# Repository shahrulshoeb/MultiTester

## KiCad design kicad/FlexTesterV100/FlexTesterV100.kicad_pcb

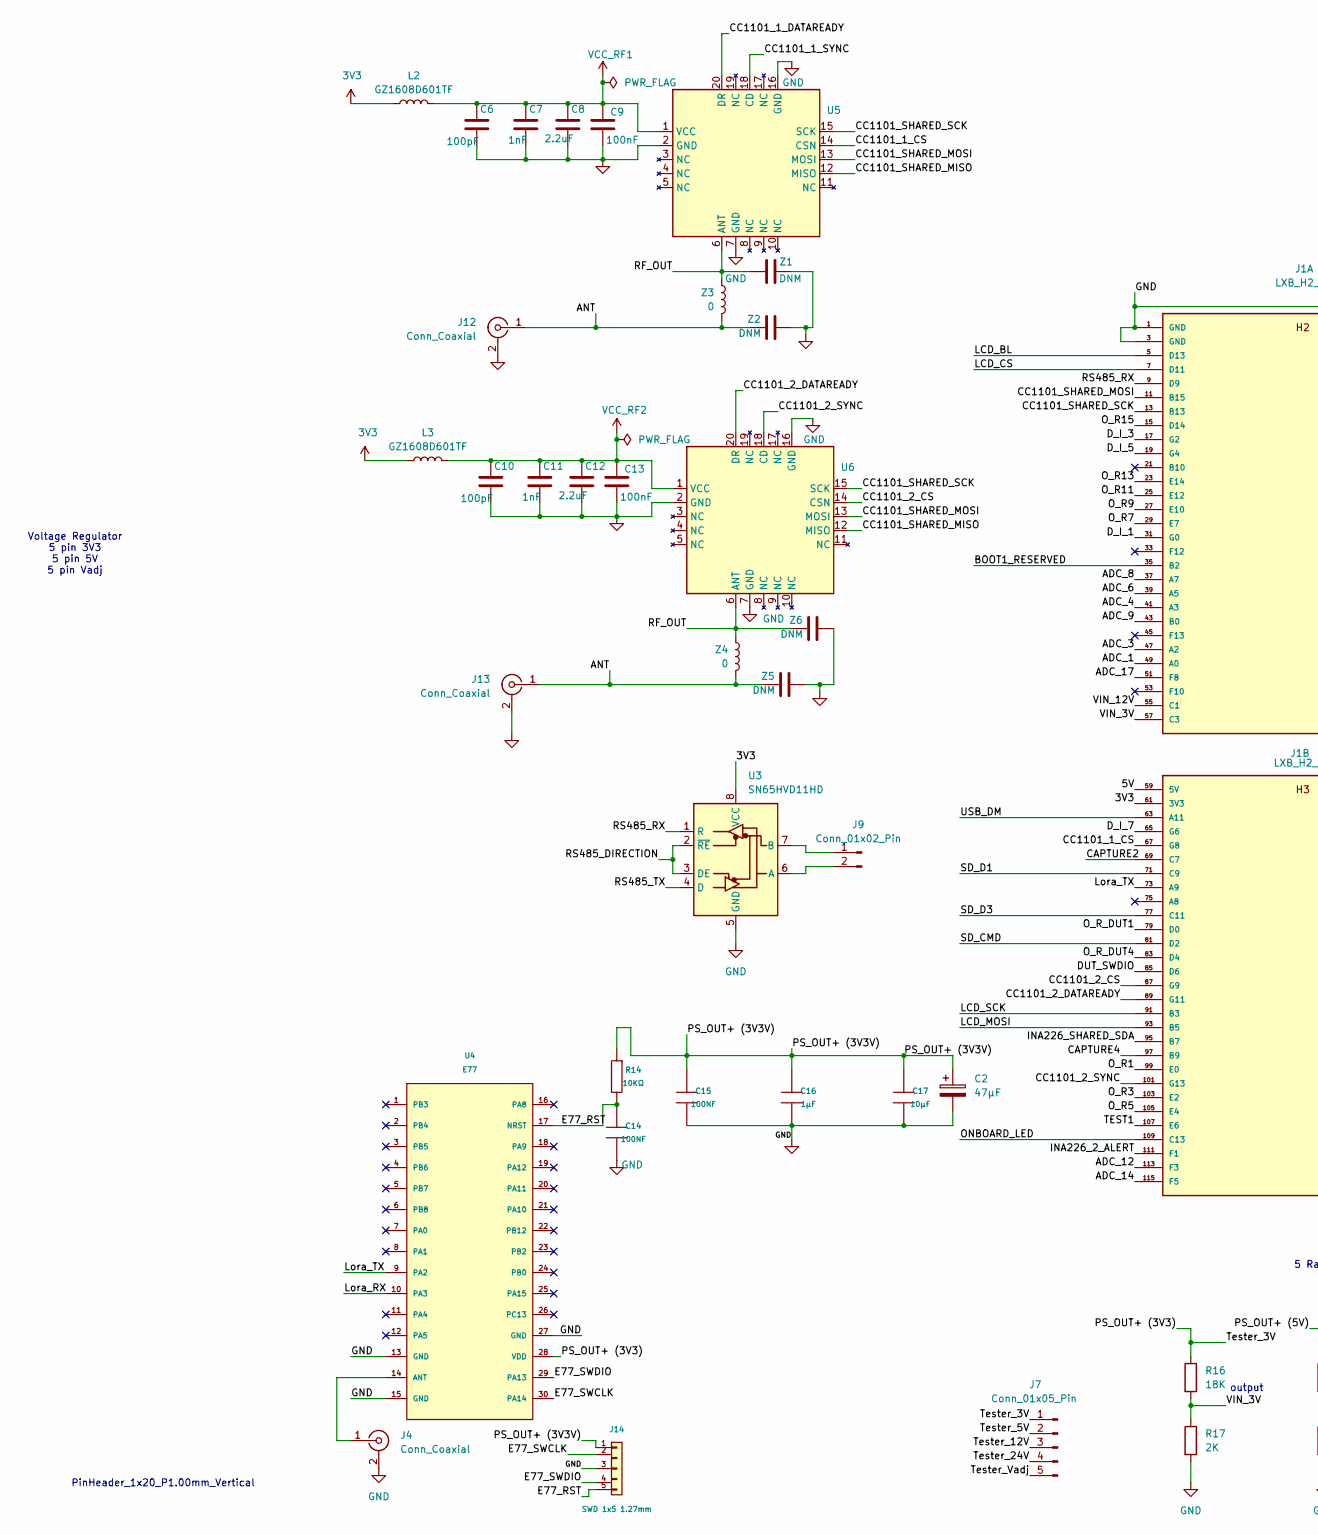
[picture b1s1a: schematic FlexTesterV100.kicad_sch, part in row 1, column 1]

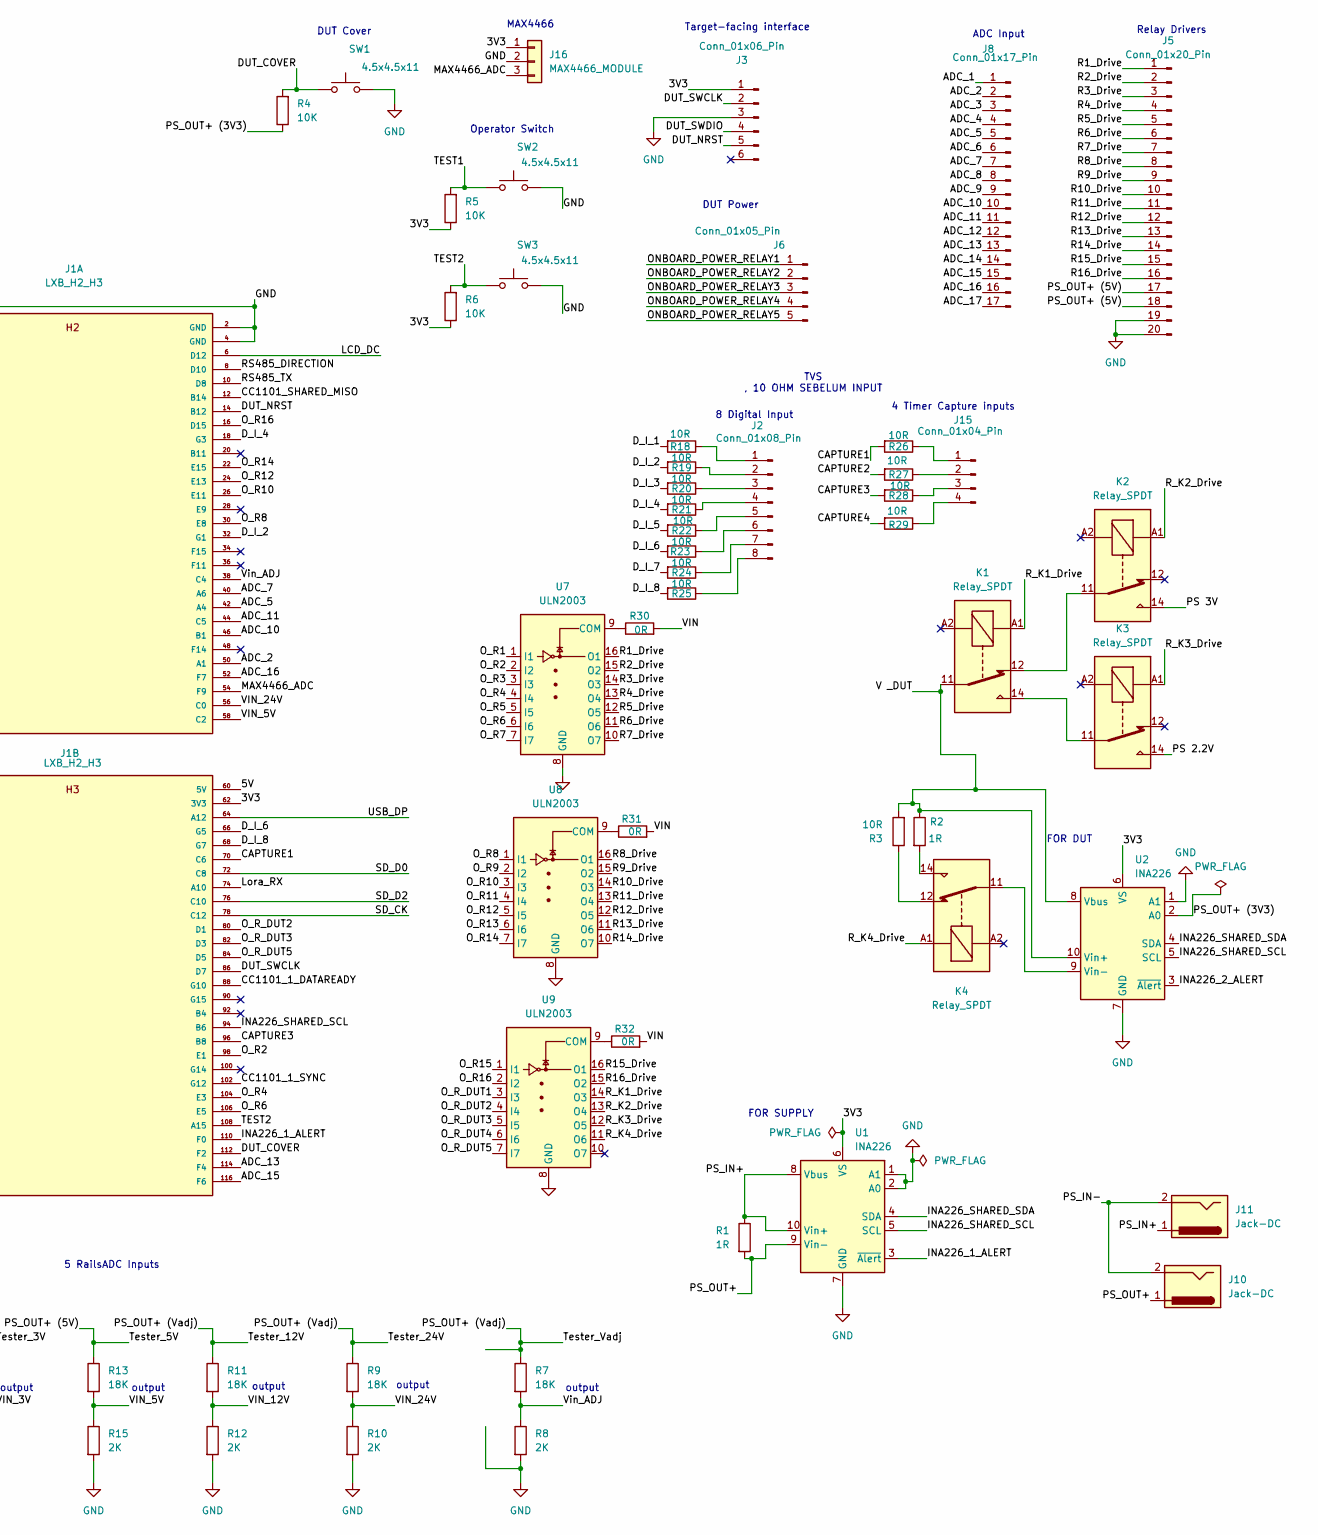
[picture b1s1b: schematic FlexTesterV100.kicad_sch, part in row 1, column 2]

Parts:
C2: 47μF; CP_EIA-7343-31_Kemet-D_HandSolder
C6, C10: 100pF; C_0603_1608Metric_Pad1.08x0.95mm_HandSolder
C7, C11: 1nF; C_0603_1608Metric_Pad1.08x0.95mm_HandSolder
C8, C12: 2.2uF; C_0603_1608Metric_Pad1.08x0.95mm_HandSolder
C9, C13: 100nF; C_0603_1608Metric_Pad1.08x0.95mm_HandSolder
C14, C15: 100NF; C0603
C16: 1μF; C0603
C17: 10μF; C0603
J1: LXB_H2_H3
J2: Conn_01x08_Pin; PinHeader_1x08_P1.00mm_Vertical
J3: Conn_01x06_Pin; PinHeader_1x06_P1.00mm_Vertical
J4, J12, J13: Conn_Coaxial; SMA_Amphenol_132203-12_Horizontal
J5: Conn_01x20_Pin; PinHeader_1x20_P1.00mm_Vertical
J6, J7: Conn_01x05_Pin; PinHeader_1x05_P1.00mm_Vertical
J8: Conn_01x17_Pin; PinHeader_1x17_P1.00mm_Vertical
J9: Conn_01x02_Pin; Terminal_2Pin_P3.50mm
J10, J11: Jack-DC
J14: SWD 1x5 1.27mm; PinHeader_1x05_P1.27mm_Vertical
J15: Conn_01x04_Pin; PinHeader_1x04_P1.00mm_Vertical
J16: MAX4466_MODULE; PinHeader_1x03_P1.00mm_Vertical
K1, K2, K3, K4: Relay_SPDT; Relay_SPDT_Hongfa_JQC-3FF_0XX-1Z
L2, L3: GZ1608D601TF; L_0603_1608Metric_Pad1.05x0.95mm_HandSolder
R1, R2: 1R; R0603
R3, R18, R19, R20, R21, R22, R23, R24, R25, R26, R27, R28, R29: 10R; R0603
R4, R5, R6: 10K; R0603
R7, R9, R11, R13, R16: 18K; R0603
R8, R10, R12, R15, R17: 2K; R0603
R14: 10KΩ; R0603
R30: 0R; R_0603_1608Metric_Pad0.98x0.95mm_HandSolder
R31, R32: 0R; R0603
SW1, SW2, SW3: 4.5x4.5x11; SW_SPST_45x45x110
U1, U2: INA226; TSSOP-10_3x3mm_P0.5mm
U3: SN65HVD11HD; SOIC-8_3.9x4.9mm_P1.27mm
U4: E77; E77-900M22S_Mark1
U5, U6: E07_400MM10_Pitch1.27mm
U7, U8, U9: ULN2003; JEITA_SOIC-16_3.9x9.9mm_P1.27mm
Z1, Z2, Z5, Z6: DNM; C_0603_1608Metric_Pad1.08x0.95mm_HandSolder
Z3, Z4: 0; L_0603_1608Metric_Pad1.05x0.95mm_HandSolder

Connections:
3V3: J1.61 (3V3), J1.62 (3V3), J3.1, J16.1, L2.1, L3.1, R5.1, R6.1, U1.6 (VS), U2.6 (VS), U3.8 (VCC)
/5V: J1.59 (5V), J1.60 (5V)
/ADC_1: J1.49 (A0), J8.1
/ADC_2: J1.50 (A1), J8.2
/ADC_3: J1.47 (A2), J8.3
/ADC_4: J1.41 (A3), J8.4
/ADC_5: J1.42 (A4), J8.5
/ADC_6: J1.39 (A5), J8.6
/ADC_7: J1.40 (A6), J8.7
/ADC_8: J1.37 (A7), J8.8
/ADC_9: J1.43 (B0), J8.9
/ADC_10: J1.46 (B1), J8.10
/ADC_11: J1.44 (C5), J8.11
/ADC_12: J1.113 (F3), J8.12
/ADC_13: J1.114 (F4), J8.13
/ADC_14: J1.115 (F5), J8.14
/ADC_15: J1.116 (F6), J8.15
/ADC_16: J1.52 (F7), J8.16
/ADC_17: J1.51 (F8), J8.17
/ANT: J12.1 (In), J13.1 (In), Z2.1, Z3.1, Z4.1, Z5.1
/BOOT1_RESERVED: J1.35 (B2)
/CAPTURE1: J1.70 (C6), R26.2
/CAPTURE2: J1.69 (C7), R27.2
/CAPTURE3: J1.96 (B8), R28.2
/CAPTURE4: J1.97 (B9), R29.2
/CC1101_1_CS: J1.67 (G8), U5.14 (CSN)
/CC1101_1_DATAREADY: J1.88 (G10), U5.20 (DR)
/CC1101_1_SYNC: J1.102 (G12), U5.18 (CD)
/CC1101_2_CS: J1.87 (G9), U6.14 (CSN)
/CC1101_2_DATAREADY: J1.89 (G11), U6.20 (DR)
/CC1101_2_SYNC: J1.101 (G13), U6.18 (CD)
/CC1101_SHARED_MISO: J1.12 (B14), U5.12 (MISO), U6.12 (MISO)
/CC1101_SHARED_MOSI: J1.11 (B15), U5.13 (MOSI), U6.13 (MOSI)
/CC1101_SHARED_SCK: J1.13 (B13), U5.15 (SCK), U6.15 (SCK)
/DUT_COVER: J1.112 (F2), R4.2, SW1.1
/DUT_NRST: J1.14 (B12), J3.5
/DUT_SWCLK: J1.86 (D7), J3.2
/DUT_SWDIO: J1.85 (D6), J3.4
/D_I_1: J1.31 (G0), R18.2
/D_I_2: J1.32 (G1), R19.2
/D_I_3: J1.17 (G2), R20.2
/D_I_4: J1.18 (G3), R21.2
/D_I_5: J1.19 (G4), R22.2
/D_I_6: J1.66 (G5), R23.2
/D_I_7: J1.65 (G6), R24.2
/D_I_8: J1.68 (G7), R25.2
/E77_RST: C14.1, J14.5, R14.2, U4.17 (NRST)
/E77_SWCLK: J14.2, U4.30 (PA14)
/E77_SWDIO: J14.4, U4.29 (PA13)
/INA226_1_ALERT: J1.110 (F0), U1.3 (~Alert)
/INA226_2_ALERT: J1.111 (F1), U2.3 (~Alert)
/INA226_SHARED_SCL: J1.94 (B6), U1.5 (SCL), U2.5 (SCL)
/INA226_SHARED_SDA: J1.95 (B7), U1.4 (SDA), U2.4 (SDA)
/LCD_BL: J1.5 (D13)
/LCD_CS: J1.7 (D11)
/LCD_DC: J1.6 (D12)
/LCD_MOSI: J1.93 (B5)
/LCD_SCK: J1.91 (B3)
/Lora_RX: J1.74 (A10), U4.10 (PA3)
/Lora_TX: J1.73 (A9), U4.9 (PA2)
/MAX4466_ADC: J1.54 (F9), J16.3
/ONBOARD_LED: J1.109 (C13)
/ONBOARD_POWER_RELAY1: J6.1
/ONBOARD_POWER_RELAY2: J6.2
/ONBOARD_POWER_RELAY3: J6.3
/ONBOARD_POWER_RELAY4: J6.4
/ONBOARD_POWER_RELAY5: J6.5
/O_R1: J1.99 (E0), U7.1 (I1)
/O_R2: J1.98 (E1), U7.2 (I2)
/O_R3: J1.103 (E2), U7.3 (I3)
/O_R4: J1.104 (E3), U7.4 (I4)
/O_R5: J1.105 (E4), U7.5 (I5)
/O_R6: J1.106 (E5), U7.6 (I6)
/O_R7: J1.29 (E7), U7.7 (I7)
/O_R8: J1.30 (E8), U8.1 (I1)
/O_R9: J1.27 (E10), U8.2 (I2)
/O_R10: J1.26 (E11), U8.3 (I3)
/O_R11: J1.25 (E12), U8.4 (I4)
/O_R12: J1.24 (E13), U8.5 (I5)
/O_R13: J1.23 (E14), U8.6 (I6)
/O_R14: J1.22 (E15), U8.7 (I7)
/O_R15: J1.15 (D14), U9.1 (I1)
/O_R16: J1.16 (D15), U9.2 (I2)
/O_R_DUT1: J1.79 (D0), U9.3 (I3)
/O_R_DUT2: J1.80 (D1), U9.4 (I4)
/O_R_DUT3: J1.82 (D3), U9.5 (I5)
/O_R_DUT4: J1.83 (D4), U9.6 (I6)
/O_R_DUT5: J1.84 (D5), U9.7 (I7)
/PS 2.2V: K3.14
/PS 3V: K2.14
/PS_IN+: J11.1, R1.1, U1.8 (Vbus), U1.10 (Vin+)
/PS_OUT+: J10.1, R1.2, U1.9 (Vin-)
/PS_OUT+ (3V3): J7.1, R4.1, R16.1, U2.2 (A0), U4.28 (VDD)
/PS_OUT+ (3V3V): C2.1, C15.1, C16.1, C17.1, J14.1, R14.1
/PS_OUT+ (5V): J5.17, J5.18, J7.2, R13.1
/PS_OUT+ (Vadj): J7.3, J7.4, J7.5, R7.1, R9.1, R11.1
/R1_Drive: J5.1, U7.16 (O1)
/R2_Drive: J5.2, U7.15 (O2)
/R3_Drive: J5.3, U7.14 (O3)
/R4_Drive: J5.4, U7.13 (O4)
/R5_Drive: J5.5, U7.12 (O5)
/R6_Drive: J5.6, U7.11 (O6)
/R7_Drive: J5.7, U7.10 (O7)
/R8_Drive: J5.8, U8.16 (O1)
/R9_Drive: J5.9, U8.15 (O2)
/R10_Drive: J5.10, U8.14 (O3)
/R11_Drive: J5.11, U8.13 (O4)
/R12_Drive: J5.12, U8.12 (O5)
/R13_Drive: J5.13, U8.11 (O6)
/R14_Drive: J5.14, U8.10 (O7)
/R15_Drive: J5.15, U9.16 (O1)
/R16_Drive: J5.16, U9.15 (O2)
/RF_OUT: U5.6 (ANT), U6.6 (ANT), Z1.2, Z3.2, Z4.2, Z6.1
/RS485_DIRECTION: J1.8 (D10), U3.2 (~RE), U3.3 (DE)
/RS485_RX: J1.9 (D9), U3.1 (R)
/RS485_TX: J1.10 (D8), U3.4 (D)
/R_K1_Drive: K1.A1, U9.14 (O3)
/R_K2_Drive: K2.A1, U9.13 (O4)
/R_K3_Drive: K3.A1, U9.12 (O5)
/R_K4_Drive: K4.A1, U9.11 (O6)
/SD_CK: J1.78 (C12)
/SD_CMD: J1.81 (D2)
/SD_D0: J1.72 (C8)
/SD_D1: J1.71 (C9)
/SD_D2: J1.76 (C10)
/SD_D3: J1.77 (C11)
/TEST1: J1.107 (E6), R5.2, SW2.1
/TEST2: J1.108 (A15), R6.2, SW3.1
/USB_DM: J1.63 (A11)
/USB_DP: J1.64 (A12)
/V _DUT: K1.11, R2.1, R3.2, U2.8 (Vbus), U2.10 (Vin+)
/VIN: R30.2, R31.2, R32.2
/VIN_3V: J1.57 (C3), R16.2, R17.1
/VIN_5V: J1.58 (C2), R13.2, R15.1
/VIN_12V: J1.55 (C1), R11.2, R12.1
/VIN_24V: J1.56 (C0), R9.2, R10.1
/Vin_ADJ: J1.38 (C4), R7.2, R8.1
GND: C2.2, C6.2, C7.2, C8.2, C9.2, C10.2, C11.2, C12.2, C13.2, C14.2, C15.2, C16.2, C17.2, J1.1 (GND), J1.2 (GND), J1.3 (GND), J1.4 (GND), J3.3, J4.2 (Ext), J5.19, J5.20, J12.2 (Ext), J13.2 (Ext), J14.3, J16.2, R8.2, R10.2, R12.2, R15.2, R17.2, SW1.2, SW2.2, SW3.2, U1.1 (A1), U1.2 (A0), U1.7 (GND), U2.1 (A1), U2.7 (GND), U3.5 (GND), U4.13 (GND), U4.15 (GND), U4.27 (GND), U5.2 (GND), U5.7 (GND), U5.16 (GND), U6.2 (GND), U6.7 (GND), U6.16 (GND), U7.8 (GND), U8.8 (GND), U9.8 (GND), Z1.1, Z2.2, Z5.2, Z6.2
unnamed: J2.1, R18.1
unnamed: J2.2, R19.1
unnamed: J2.3, R20.1
unnamed: J2.4, R21.1
unnamed: J2.5, R22.1
unnamed: J2.6, R23.1
unnamed: J2.7, R24.1
unnamed: J2.8, R25.1
unnamed: J4.1 (In), U4.14 (ANT)
unnamed: J9.1, U3.7 (B)
unnamed: J9.2, U3.6 (A)
unnamed: J10.2, J11.2
unnamed: J15.1, R26.1
unnamed: J15.2, R27.1
unnamed: J15.3, R28.1
unnamed: J15.4, R29.1
unnamed: K1.12, K2.11
unnamed: K1.14, K3.11
unnamed: K4.12, R3.1
unnamed: K4.14, R2.2
unnamed: K4.11, U2.9 (Vin-)
unnamed: R30.1, U7.9 (COM)
unnamed: R31.1, U8.9 (COM)
unnamed: R32.1, U9.9 (COM)
VCC_RF1: C6.1, C7.1, C8.1, C9.1, L2.2, U5.1 (VCC)
VCC_RF2: C10.1, C11.1, C12.1, C13.1, L3.2, U6.1 (VCC)

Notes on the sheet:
Voltage Regulator 5 pin 3V3 5 pin 5V 5 pin Vadj
Relay Drivers
8 Digital Input
PinHeader_1x20_P1.00mm_Vertical
MAX4466
ADC Input
DUT Power
Operator Switch
output
5 RailsADC Inputs
DUT Cover
FOR SUPPLY
Target-facing interface
FOR DUT
4 Timer Capture inputs
TVS , 10 OHM SEBELUM INPUT

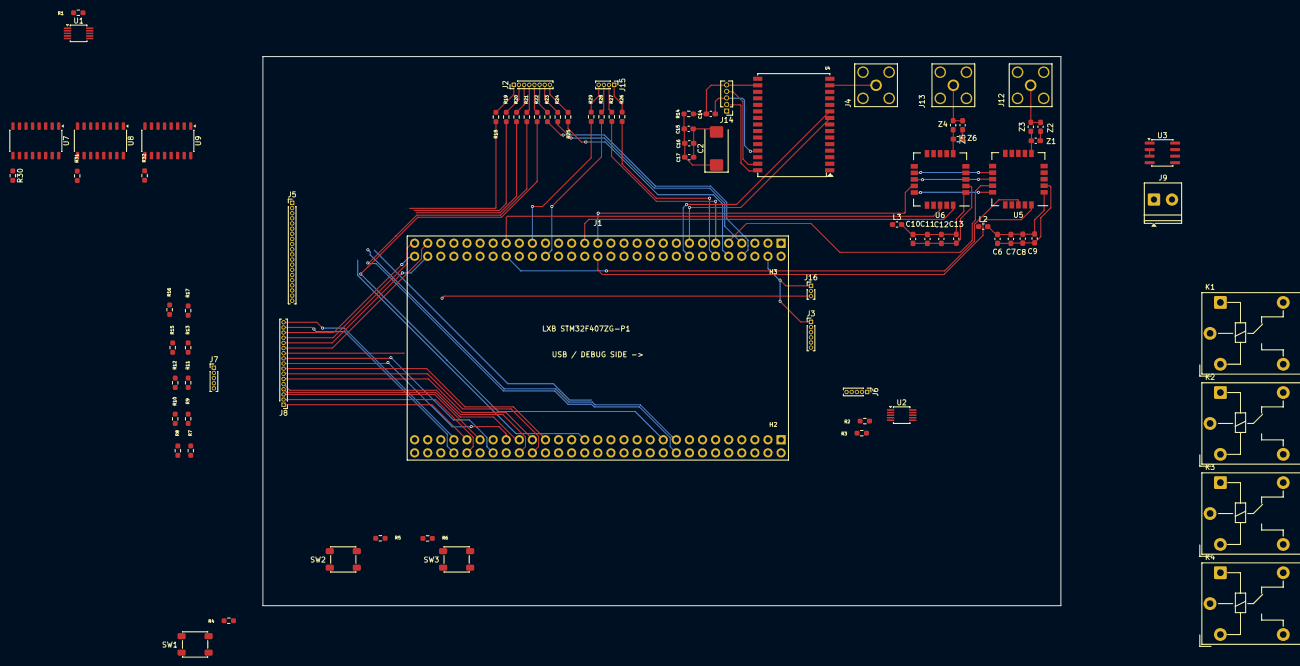
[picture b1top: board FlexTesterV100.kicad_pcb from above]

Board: 2 copper layers, 154.9 x 106.6 mm, 83 parts (0 on the bottom side), 141 nets.
